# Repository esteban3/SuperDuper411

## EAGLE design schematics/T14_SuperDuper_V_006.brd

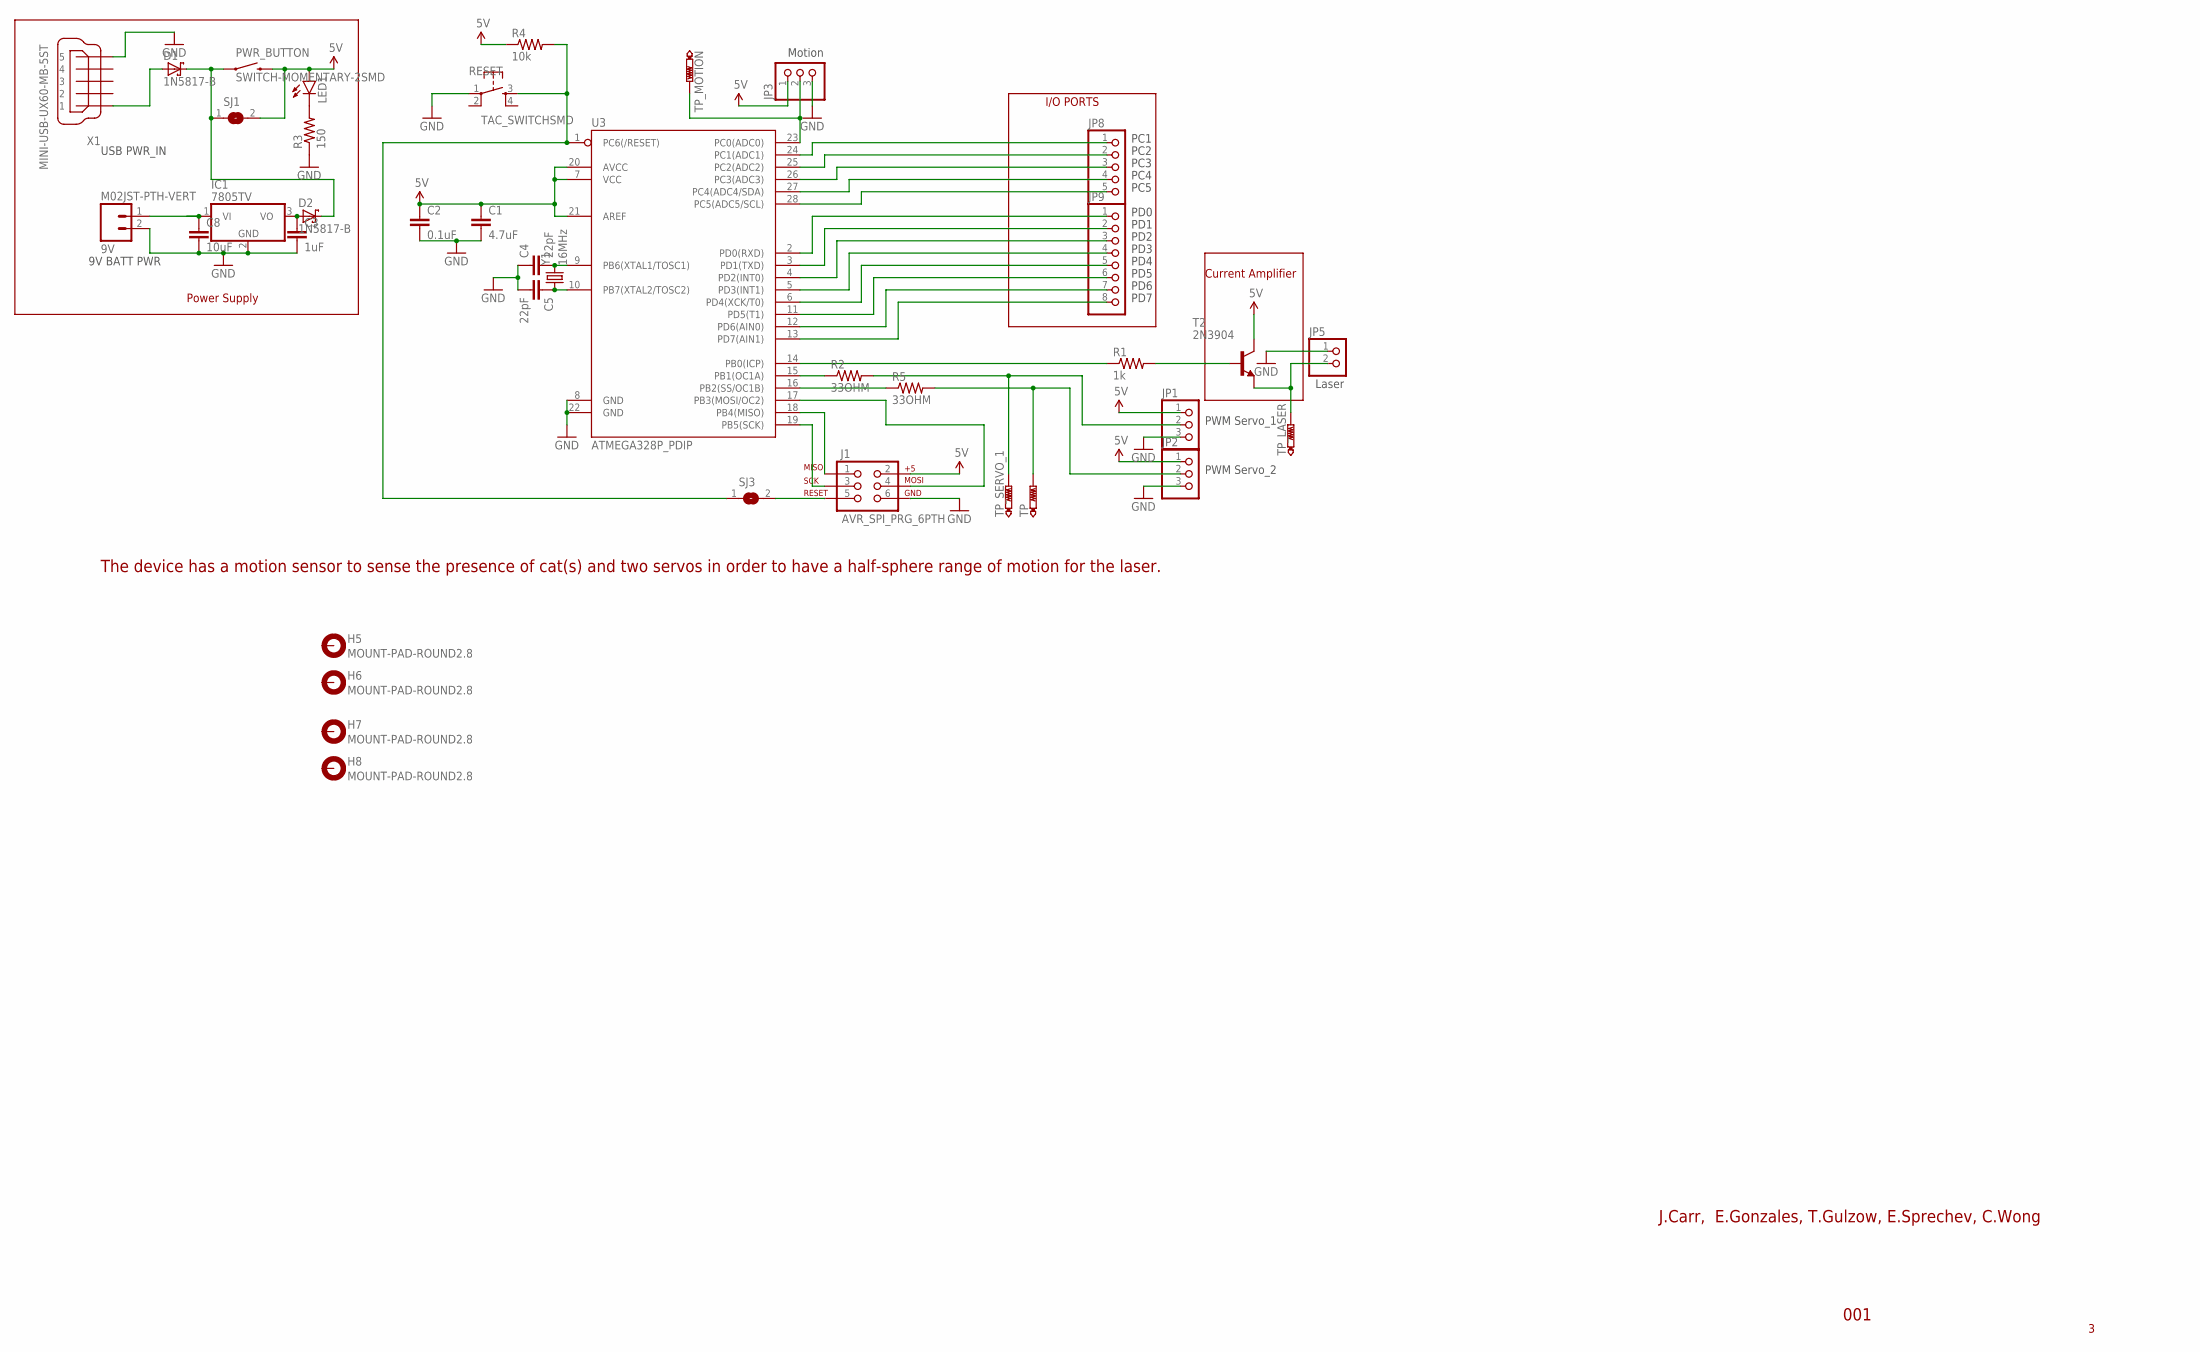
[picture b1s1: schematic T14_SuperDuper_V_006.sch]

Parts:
9V: M02JST-PTH-VERT; JST-2-PTH-VERT
C1: 4.7uF; 0603-CAP
C2: 0.1uF; 0603-CAP
C3: 1uF; 0603-CAP
C4, C5: 22pF; 0603-CAP
C8: 10uF; 0603-CAP
D1, D2: 1N5817-B; DO41-7.6
H5, H6, H7, H8: MOUNT-PAD-ROUND2.8; 2,8-PAD
IC1: 7805TV; TO220V
J1: AVR_SPI_PRG_6PTH; 2X3
JP1, JP2, JP3: PINHD-1X3; 1X03
JP5: PINHD-1X2; 1X02
JP8: PINHD-1X5; 1X05
JP9: PINHD-1X8; 1X08
LED1: LED-3MM-NO_SILK; LED3MM-NS
PWR_BUTTON: SWITCH-MOMENTARY-2SMD; TACTILE-SWITCH-SMD
R1: 1k; 0603
R2, R5: 33OHM; 0603
R3: 150; 0603
R4: 10k; 0603
RESET: TAC_SWITCHSMD; TACTILE-SWITCH-SMD
SJ1, SJ3: SJ
T2: 2N3904; TO92
TP: PTR1B2,54; B2,54
TP_LASER: PTR1B2,54; B2,54
TP_MOTION: PTR1B2,54; B2,54
TP_SERVO_1: PTR1B2,54; B2,54
U3: ATMEGA328P_PDIP; DIL28-3
X1: MINI-USB-UX60-MB-5ST; UX60-MB-5ST
Y1: 16MHz; CRYSTAL-SMD-10.5X4.8-2PIN

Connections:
5V: C1.1, C2.1, J1.2, JP1.1, JP2.1, JP3.1, LED1.A, PWR_BUTTON.3 (2), R4.1, SJ1.2, T2.1 (C), U3.7 (VCC), U3.20 (AVCC), U3.21 (AREF)
GND: 9V.2, C1.2, C2.2, C3.2, C4.1, C5.2, C8.2, IC1.2 (GND), J1.6, JP1.3, JP2.3, JP3.3, JP5.1, R3.1, RESET.1, U3.8 (GND), U3.22 (GND), X1.5
unnamed: D1.A, X1.1
unnamed: R2.1, U3.15 (PB1(OC1A))
unnamed: R1.2, T2.2 (B)
unnamed: JP1.2, R2.2, TP_SERVO_1.TP
unnamed: C5.1, U3.10 (PB7(XTAL2/TOSC2)), Y1.P$1 (1)
unnamed: R5.1, U3.16 (PB2(SS/OC1B))
unnamed: JP2.2, R5.2, TP.TP
unnamed: 9V.1, C8.1, IC1.1 (VI)
unnamed: R1.1, U3.14 (PB0(ICP))
unnamed: C3.1, D2.A, IC1.3 (VO)
unnamed: J1.4, U3.17 (PB3(MOSI/OC2))
unnamed: J1.1, U3.18 (PB4(MISO))
unnamed: J1.3, U3.19 (PB5(SCK))
unnamed: R4.2, RESET.3, SJ3.1, U3.1 (PC6(/RESET))
unnamed: JP3.2, TP_MOTION.TP, U3.23 (PC0(ADC0))
unnamed: C4.2, U3.9 (PB6(XTAL1/TOSC1)), Y1.P$2 (2)
unnamed: JP8.5, U3.28 (PC5(ADC5/SCL))
unnamed: JP8.4, U3.27 (PC4(ADC4/SDA))
unnamed: JP8.3, U3.26 (PC3(ADC3))
unnamed: JP8.2, U3.25 (PC2(ADC2))
unnamed: JP8.1, U3.24 (PC1(ADC1))
unnamed: JP9.1, U3.2 (PD0(RXD))
unnamed: JP9.2, U3.3 (PD1(TXD))
unnamed: JP9.3, U3.4 (PD2(INT0))
unnamed: JP9.4, U3.5 (PD3(INT1))
unnamed: JP9.5, U3.6 (PD4(XCK/T0))
unnamed: JP9.6, U3.11 (PD5(T1))
unnamed: JP9.7, U3.12 (PD6(AIN0))
unnamed: JP9.8, U3.13 (PD7(AIN1))
unnamed: JP5.2, T2.3 (E), TP_LASER.TP
unnamed: D1.C, D2.C, PWR_BUTTON.1, SJ1.1
unnamed: J1.5, SJ3.2
unnamed: LED1.K (C), R3.2

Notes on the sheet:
Laser
PWM Servo_1
PWM Servo_2
Motion
9V BATT PWR
USB PWR_IN
J.Carr, E.Gonzales, T.Gulzow, E.Sprechev, C.Wong
001
Power Supply
PC1
PC2
PC3
PC4
PC5
PD0
PD1
PD2
PD3
PD4
PD5
PD6
PD7
I/O PORTS
The device has a motion sensor to sense the presence of cat(s) and two servos in order to have a half-sphere range of motion for the laser.
Current Amplifier

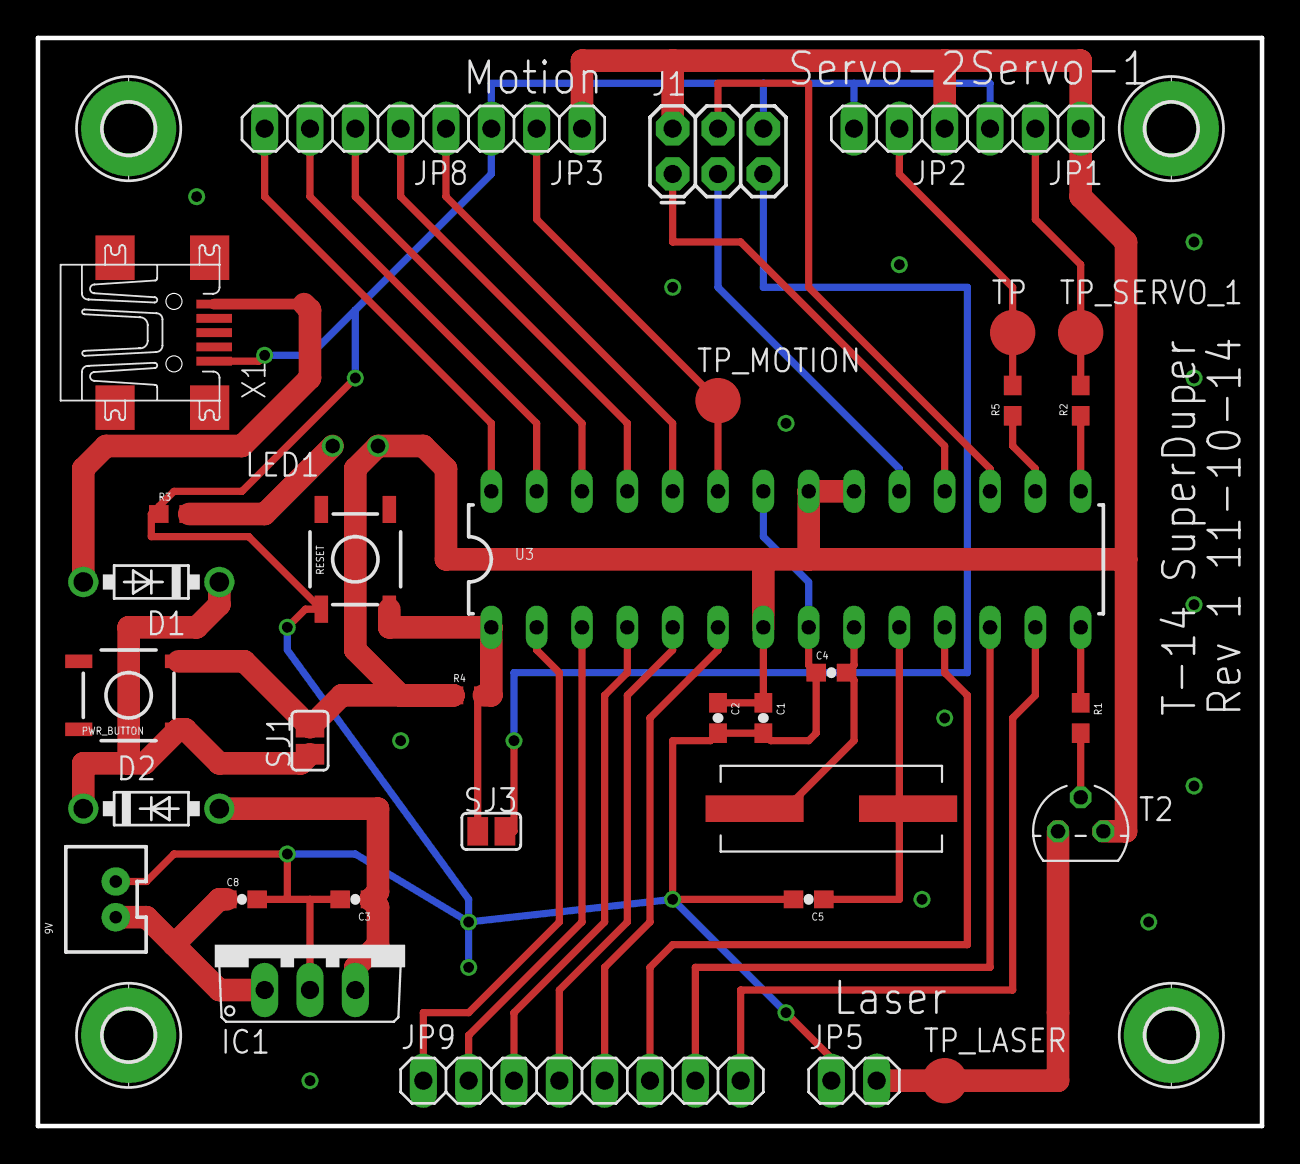
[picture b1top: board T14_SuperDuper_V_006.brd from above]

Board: 2 copper layers, 68.6 x 61.0 mm, 39 parts (0 on the bottom side), 35 nets.

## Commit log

2014-10-13 added homework folder
2014-10-29 T14_SuperDuperPrelimSchematic
    Preliminary Schematic
2014-10-30 Revised schematic
    Revised for proper layering, adding frame, correcting placement of
    bypass caps
2014-10-30 Added power button & jumpers on board schematic
2014-11-03 Logo :)
2014-11-03 Added Schematics folder
2014-11-03 Added images folder
2014-11-03 Adding bom
2014-11-04 Updated schematic per Andrew Greenberg's recommendations
2014-11-04 Bill of Materials
2014-11-04 Revert "Updated schematic per Andrew Greenberg's recommendations"
    This reverts commit 7f5d9ebcb568cb28b67e02d461c7676f40850b36.
2014-11-04 Updated schematic
    Updated schematic per Andrew Greenberg's recommendations of 11-3-14
2014-11-04 T14_PrototypeLayout
    Prototype Layout on Breadboard
2014-11-04 Trying to consolidate schematics folder
2014-11-04 Updated WPR
2014-11-04 Updated WPF
2014-11-04 Compiled parts info
2014-11-04 Created Project Schedule
2014-11-04 Rough sketch of project timing
2014-11-05 Code for rotating laser
2014-11-05 Prelim Board Layout
2014-11-05 Schematic corresponding to prelim board layout
2014-11-06 Renamed schematic to match board layout
2014-11-06 Renamed board layout to match schematic
2014-11-06 Updated schematic & board layout
2014-11-10 Converted Project Schedule from Excel to MS Project
2014-11-11 Updated Project Schedule
2014-11-11 Uploaded updated schematics & board layouts
2014-11-14 code takes sensor input from a random pin now.
    TODO: MAKE SURE THAT THE PIN GETS CHANGED TO THE MOTION DETECTOR PIN.
2014-11-14 Uploaded weekly progress reports
2014-11-14 Uploaded wpr
2014-11-14 Autocad drawing of platform design w/in housing
2014-11-14 Recreated folder for encasement
2014-11-17 Homework5_ProjectModel_ParkingMeterExample
2014-11-17 blblblblblblaaaa
2014-11-17 Deleted example commit file
2014-11-18 Update to the code
    All is working on our current prototype, but we need to test the code on hardware that has the correct clock frequency.
2014-11-23 Uploaded template for test cases
2014-11-24 stuff
    this thing hates me
2014-11-24 Update BOM and Specs
    include datasheets and order info
2014-11-24 Test documents
    new test plan documents
2014-11-24 Uploaded Requirements Spec
2014-11-24 Uploaded Test Plan & Test Cases
2014-12-03 Hopefully the final update to the code
    Laser pin turns off when the servers turn off. Servos now run slower, and have a 3 second cooldown after being triggered.
2014-12-03 Corrected date on Esteban's WPR
2014-12-10 Modified code for smaller angles; added commenting
2014-12-11 PowerPoint Presentation
2014-12-11 Final WPR
2014-12-11 Updated Requirements Doc
2014-12-11 Uploaded Esteban's WPR
2014-12-11 WPR update
    the last couple of weeks
2014-12-11 Updated BOM
2014-12-11 Updated PPT
2014-12-11 Updated finished product images
2014-12-12 Uploaded Tim's WPR
2014-12-12 Uploaded final report

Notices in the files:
parts and their libraries:
SparkFun-Capacitors: Licensing: Creative Commons ShareAlike 4.0 International - https://creativecommons.org/licenses/by-sa/4.0
